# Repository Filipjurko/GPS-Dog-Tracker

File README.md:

# GPS-Dog-Tracker
This repsitory contains pcb designs, arduino code and 3D designed housing for this open source GPS Dog Tracker. This project is protected by Creative Commons of Attribution and NoDerivatives (CC-BY-ND)

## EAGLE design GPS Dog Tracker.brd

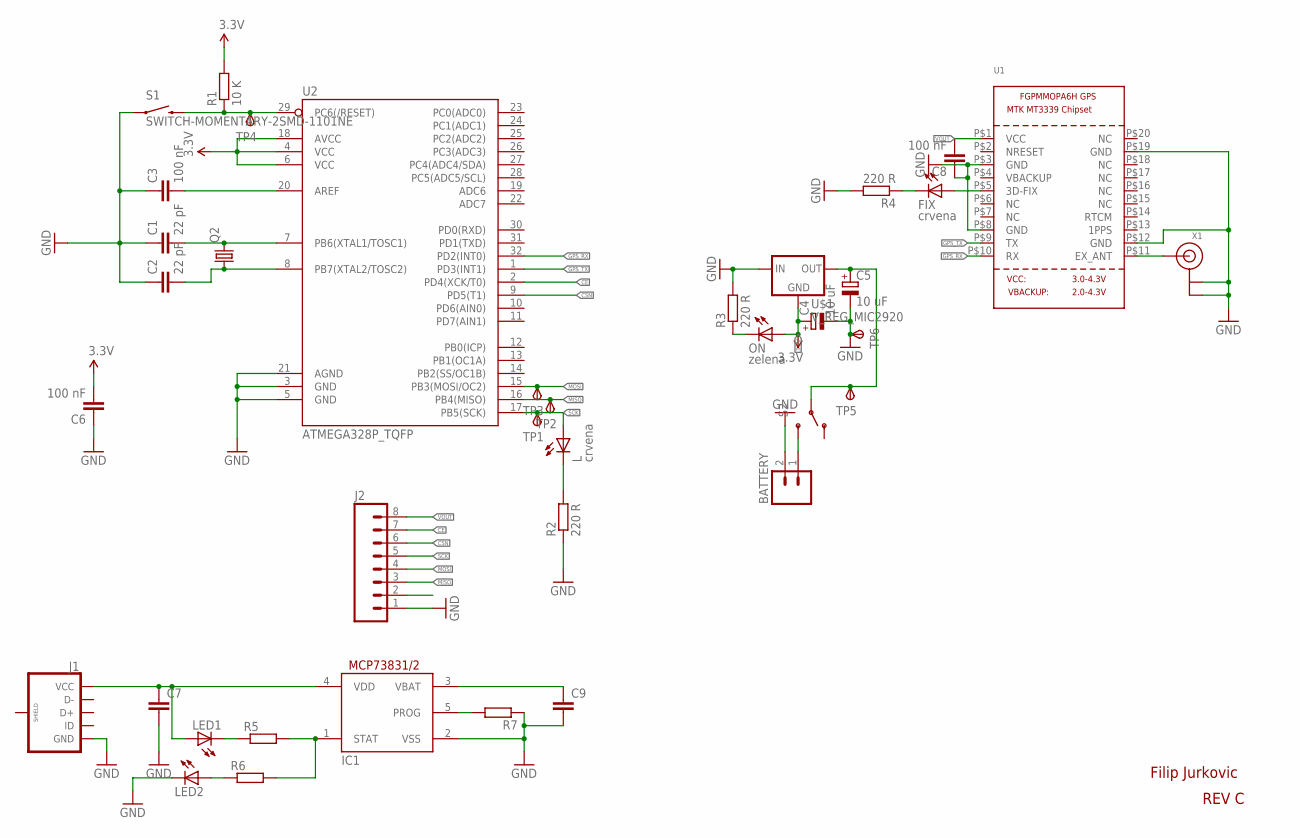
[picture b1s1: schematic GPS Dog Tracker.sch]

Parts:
BATTERY: M021X02_NO_SILK; 1X02_NO_SILK
C1, C2: 22 pF; C0603
C3, C6, C8: 100 nF; C0603
C4, C5: 10 uF; SMC_A
C7, C9: C-EUC0603; C0603
FIX: crvena; CHIP-LED0805
IC1: MCP73831/OT; SOT23-5L
J1: USB_MICROB_PLUGCONN-11752; USB-B-MICRO-SMD_V03
J2: M08SILK_FEMALE_PTH; 1X08
L: crvena; CHIP-LED0805
LED1, LED2: LEDCHIPLED_0805; CHIPLED_0805
ON: zelena; CHIP-LED0805
Q2: CRYSTALHC49S; HC49/S
R1: 10 K; R0603
R2, R3, R4: 220 R; R0603
R5, R6, R7: R-EU_R0603; R0603
S1: SWITCH-MOMENTARY-2SMD-1101NE; TACTILE-SWITCH-1101NE
S2: SWITCH-SPDT-SMD-A; SWITCH-SPST-SMD-A
TP1, TP2, TP3, TP4, TP5, TP6: TPSTP13R; TP13R
U1: GPS_FGPMMOPA6H; FGPMMOPA6H
U2: ATMEGA328P_TQFP; TQFP32-08
U$1: V_REG_MIC2920; SOT223
X1: ANTENNA_U.FL; U.FL

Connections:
3.3V: C4.+, C6.2, ON.A, R1.2, U2.4 (VCC), U2.6 (VCC), U2.18 (AVCC), U$1.2 (GND)
CE: J2.7, U2.2 (PD4(XCK/T0))
CSN: J2.6, U2.9 (PD5(T1))
GND: BATTERY.2, C1.1, C2.1, C3.1, C4.-, C5.-, C6.1, C7.2, C8.1, C9.2, IC1.2 (VSS), J1.GND, J2.1, LED2.C, R2.1, R3.2, R4.2, R7.1, S1.1, TP6.TP, U1.P$3 (GND), U1.P$8 (GND), U1.P$12 (GND), U1.P$19 (GND), U2.3 (GND), U2.5 (GND), U2.21 (AGND), U$1.1 (IN), X1.1 (GND), X1.2 (GND)
GPS_RX: U1.P$10 (RX), U2.32 (PD2(INT0))
GPS_TX: U1.P$9 (TX), U2.1 (PD3(INT1))
MISO: J2.3, TP2.TP, U2.16 (PB4(MISO))
MOSI: J2.4, TP3.TP, U2.15 (PB3(MOSI/OC2))
unnamed: C1.2, Q2.2, U2.7 (PB6(XTAL1/TOSC1))
unnamed: C2.2, Q2.1, U2.8 (PB7(XTAL2/TOSC2))
unnamed: C3.2, U2.20 (AREF)
unnamed: ON.C, R3.1
unnamed: FIX.A, U1.P$5 (3D-FIX)
unnamed: FIX.C, R4.1
unnamed: L.C, R2.2
unnamed: IC1.1 (STAT), R5.2, R6.2
unnamed: LED1.C, R5.1
unnamed: LED2.A, R6.1
unnamed: U1.P$11 (EX_ANT), X1.3 (SIGNAL)
unnamed: IC1.5 (PROG), R7.2
RESET: R1.1, S1.2, TP4.TP, U2.29 (PC6(/RESET))
SCK: J2.5, L.A, TP1.TP, U2.17 (PB5(SCK))
VIN: BATTERY.1, C9.1, IC1.3 (VBAT), S2.3 (S)
VIN1: C5.+, C7.1, IC1.4 (VDD), J1.VBUS (VCC), LED1.A, S2.2, TP5.TP, U$1.3 (OUT)
VOUT: C8.2, J2.8, U1.P$1 (VCC)

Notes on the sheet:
Filip Jurkovic
REV C

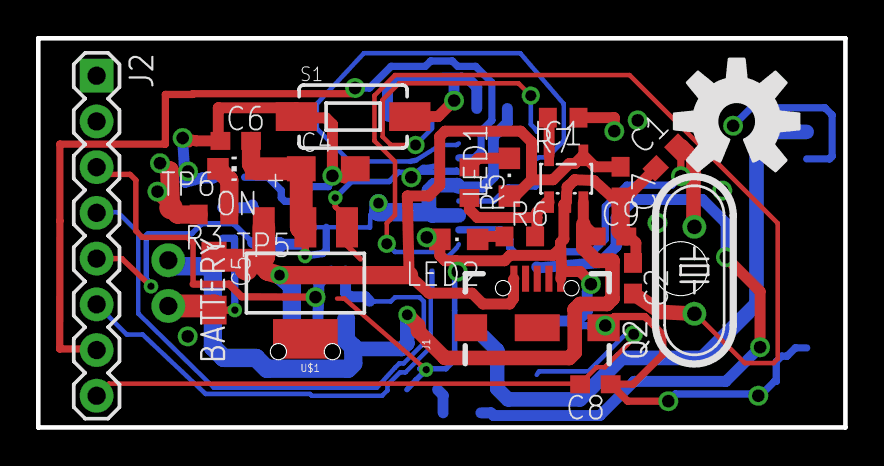
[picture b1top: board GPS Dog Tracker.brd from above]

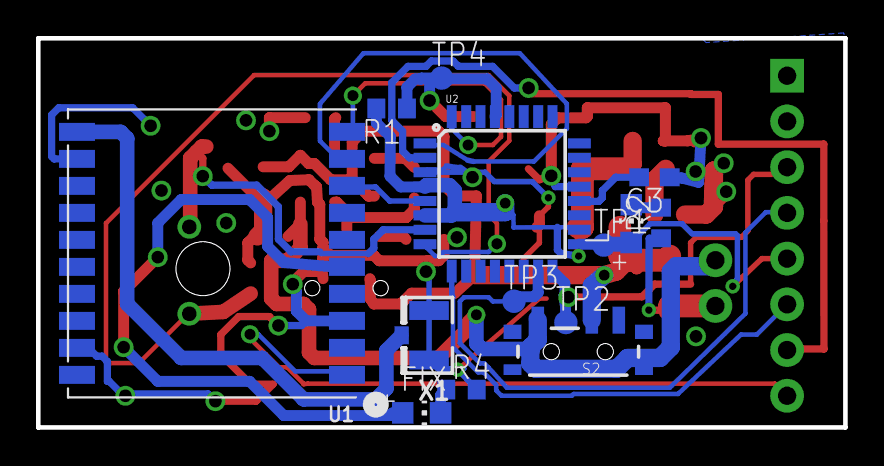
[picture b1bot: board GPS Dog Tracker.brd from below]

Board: 2 copper layers, 44.8 x 21.6 mm, 39 parts (14 on the bottom side), 25 nets.

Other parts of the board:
U$2: OSHW-LOGO-L

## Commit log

2016-07-16 PCB Designs
2016-07-16 PCB Designs
    This folder contains both transmitter and receiver for the dog tracker

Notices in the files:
parts and their libraries:
SparkFun-Connectors: Licensing: Creative Commons ShareAlike 4.0 International - https://creativecommons.org/licenses/by-sa/4.0
